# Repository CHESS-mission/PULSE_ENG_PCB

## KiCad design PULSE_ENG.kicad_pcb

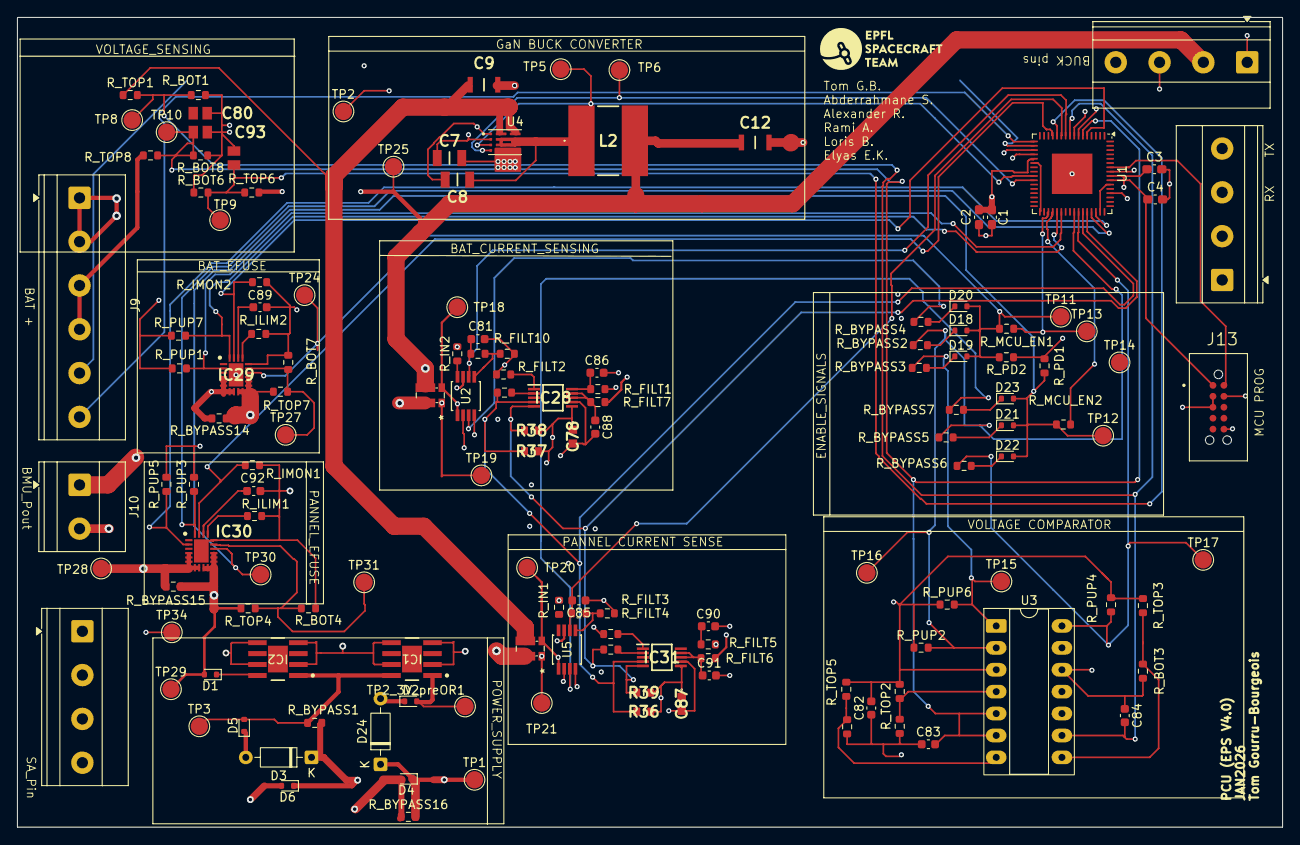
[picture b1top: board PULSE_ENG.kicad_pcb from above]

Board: 4 copper layers, 146.7 x 93.9 mm, 144 parts (0 on the bottom side), 84 nets.

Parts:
C1, C4: 100nF; C_0603_1608Metric_Pad1.08x0.95mm_HandSolder
C2, C3: 10uF; C_0603_1608Metric_Pad1.08x0.95mm_HandSolder
C7, C8: CAPC3216X170N
C9: 4.7uF; CAPC3216X180N
C12: C3216X8L1E106K160AE; CAPC3216X180N
C78, C87: 0.1μF; C0603
C79, C80, C93: 10nF; CAPC2012X145N
C81, C82, C83, C84, C85, C86, C88, C89, C90, C91, C92: 100nF; C_0603_1608Metric
D1, D2, D4, D5, D6, D18, D19, D20, D21, D22, D23: 1N4148WT; D_SOD-523
D3, D24: 1N5711; D_DO-35_SOD27_P7.62mm_Horizontal
IC1: TPS7B8733QDDARQ1; DDA0008J-IPC_B
IC2: TPS7B8750QDDARQ1; DDA0008J-IPC_B
IC28, IC31: INA226AIDGSR; SOP50P490X110-10N
IC29, IC30: TPS25940ARVCR; QFN50P300X400X80-21N
J8, J11, J12: Screw_Terminal_01x04; TerminalBlock_Phoenix_MKDS-1,5-4-5.08_1x04_P5.08mm_Horizont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
J9: Screw_Terminal_01x06; TerminalBlock_Phoenix_MKDS-1,5-6-5.08_1x06_P5.08mm_Horizont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
J10: Screw_Terminal_01x01; TerminalBlock_Phoenix_MKDS-1,5-2-5.08_1x02_P5.08mm_Horizont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
J13: TC2050-IDC-NL; TAG-CONNECT_TC2050-IDC-NL
L2: 78404084470
R36, R37, R38, R39: 10KΩ; RESC1608X55N
R_ADD_CONFIG1, R_ADD_CONFIG2, R_ADD_CONFIG3, R_ADD_CONFIG4: 0; R_0603_1608Metric
R_BAT_SHUNT1: 20mOhm; R_Shunt_Vishay_WSKW0612
R_BOT1, R_BOT2, R_BOT3, R_BOT5, R_BOT6, R_BOT8: 180k; R_0603_1608Metric
R_BOT4, R_BOT7: 100k; R_0603_1608Metric
R_BYPASS1, R_BYPASS2, R_BYPASS3, R_BYPASS4, R_BYPASS5, R_BYPASS6, R_BYPASS7, R_BYPASS14, R_BYPASS15, R_BYPASS16: 0; R_0603_1608Metric
R_FILT1, R_FILT5, R_FILT6, R_FILT7: 10; R_0603_1608Metric
R_FILT2, R_FILT4: 2.61k; R_0603_1608Metric
R_FILT3, R_FILT10: 402; R_0603_1608Metric
R_ILIM1: 24k; R_0603_1608Metric
R_ILIM2: 16.9k; R_0603_1608Metric
R_IMON1, R_IMON2: 4k; R_0603_1608Metric
R_IN1, R_IN2: 100; R_0603_1608Metric
R_MCU_EN1, R_MCU_EN2: 1k; R_0603_1608Metric
R_PANNEL_SHUNT1: 20mOhm; R_Shunt_Vishay_WSKW0612
R_PD1, R_PD2: 100k; R_0603_1608Metric
R_PUP1, R_PUP2, R_PUP3, R_PUP4, R_PUP5, R_PUP6, R_PUP7: 10k; R_0603_1608Metric
R_TOP1, R_TOP6, R_TOP8: 680k; R_0603_1608Metric
R_TOP2: 147k; R_0603_1608Metric
R_TOP3: 68k; R_0603_1608Metric
R_TOP4, R_TOP7: 681; R_0603_1608Metric
R_TOP5: 247k; R_0603_1608Metric
TP1: 3V3_rail; TestPoint_Pad_D2.0mm
TP2: 12Vin_buck; TestPoint_Pad_D2.0mm
TP2_3V_preOR1: TestPoint_Pad_D2.0mm
TP3: 5V_preOR; TestPoint_Pad_D2.0mm
TP5: PWM_H; TestPoint_Pad_D2.0mm
TP6: PWM_L; TestPoint_Pad_D2.0mm
TP8: VPANNEL_SENSE; TestPoint_Pad_D2.0mm
TP9: VCHG_RAIL_SENSE; TestPoint_Pad_D2.0mm
TP10: VBAT_SENSE; TestPoint_Pad_D2.0mm
TP11: BAT_EFUSE_EN; TestPoint_Pad_D2.0mm
TP12: PANNEL_EFUSE_EN; TestPoint_Pad_D2.0mm
TP13: MCU_BAT_EFUSE_EN; TestPoint_Pad_D2.0mm
TP14: MCU_PANNEL_EFUSE_EN; TestPoint_Pad_D2.0mm
TP15: BAT_UVP; TestPoint_Pad_D2.0mm
TP16: BAT_OVP; TestPoint_Pad_D2.0mm
TP17: PANNEL_OVP; TestPoint_Pad_D2.0mm
TP18: BAT_SHUNT_OUT; TestPoint_Pad_D2.0mm
TP19: BAT_SHUNT_IN; TestPoint_Pad_D2.0mm
TP20: PANNEL_SHUNT_OUT; TestPoint_Pad_D2.0mm
TP21: PANNEL_SHUNT_IN; TestPoint_Pad_D2.0mm
TP24: eFUSE_EN; TestPoint_Pad_D2.0mm
TP25: Buck_out; TestPoint_Pad_D2.0mm
TP27: eFUSE_OVP; TestPoint_Pad_D2.0mm
TP28: P_Vout_Protected; TestPoint_Pad_D2.0mm
TP29: PVin; TestPoint_Pad_D2.0mm
TP30: eFuse_EN; TestPoint_Pad_D2.0mm
TP31: eFuse_OVP; TestPoint_Pad_D2.0mm
TP34: GND; TestPoint_Pad_D2.0mm
U1: ATSAMD21J17D-M; QFN-64-1EP_9x9mm_P0.5mm_EP4.7x4.7mm
U2, U5: LT6108IMS8-1-TRPBF; MSOP-8_MS_LIT
U3: LM139ADRG4; CERDIP-14_W7.62mm_SideBrazed_LongPads_Socket
U4: EPC2152; VREG_EPC2152ENGRT

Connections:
12V_1: C7.1, J11.1, TP2.1, U4.2 (Vdd12)
/3.3V: C78.1, IC28.6 (VS), R37.2, R38.2, R_PUP1.2, R_PUP7.2
/5V: D3.1 (K), D6.1 (K), R_BYPASS1.2
/BAT_EFUSE_EN: D18.2 (A), D19.2 (A), D20.2 (A), IC29.14 (EN), R_MCU_EN1.1, R_PD2.2, TP11.1, TP24.1
/BAT_EFUSE_FLT: IC29.20 (~FLT), R_PUP7.1, U1.37 (PA18)
/BAT_EFUSE_IMON: IC29.19 (IMON), R_IMON2.2, U1.5 (PB04)
/BAT_EFUSE_PGOOD: IC29.2 (PGOOD), R_PUP1.1, U1.38 (PA19)
/BAT_OVP_FLAG: R_BYPASS2.1, R_BYPASS5.1, R_PUP2.2, TP16.1, U1.41 (PA20), U3.2 (2OUT)
/BAT_SHUNT_IN: R_BAT_SHUNT1.3, R_FILT1.1, R_IN2.2, TP19.1, U2.7 (V+)
/BAT_SHUNT_OUT: R_BAT_SHUNT1.2, R_FILT7.1, TP18.1, U2.1 (SENSELO)
/BAT_UVP_FLAG: R_BYPASS3.1, R_PUP6.2, TP15.1, U3.1 (1OUT)
/Battery_protection_and_sensing/P_Vout_Protected: IC29.4 (OUT_1), IC29.5 (OUT_2), IC29.6 (OUT_3), IC29.7 (OUT_4), IC29.8 (OUT_5), J10.1, R_BYPASS14.2
/EPS_Power_Supply/3V3_LDO: D2.2 (A), IC1.1 (OUT), TP2_3V_preOR1.1
/EPS_Power_Supply/5V_LDO: D5.2 (A), IC1.8 (IN), IC2.1 (OUT), R_BYPASS1.1, TP3.1
/GAN_PWM_H: TP5.1, U1.25 (PB12), U4.3 (HSin)
/GAN_PWM_L: TP6.1, U1.26 (PB13), U4.4 (LSin)
/HEATER_SWITCH: J9.6, U1.17 (PA08)
/I_BAT_ANA: C81.2, R_FILT10.2, U1.10 (PB07), U2.6 (OUTA)
/I_PANNEL_ANA: C85.2, R_FILT3.2, U1.11 (PB08), U5.6 (OUTA)
/MCU_BAT_EFUSE_EN: R_MCU_EN1.2, TP13.1, U1.35 (PA16)
/MCU_PANNEL_EFUSE_EN: R_MCU_EN2.2, TP14.1, U1.36 (PA17)
/PANNEL_EFUSE_EN: D21.2 (A), D22.2 (A), D23.2 (A), IC30.14 (EN), R_MCU_EN2.1, R_PD1.2, TP12.1, TP30.1
/PANNEL_OVP_FLAG: R_BYPASS6.1, R_PUP4.1, TP17.1, U1.42 (PA21), U3.14 (OUT3)
/PANNEL_SHUNT_IN: R_FILT6.1, R_IN1.2, R_PANNEL_SHUNT1.3, TP21.1, U5.7 (V+)
/PANNEL_SHUNT_OUT: R_FILT5.1, R_PANNEL_SHUNT1.2, TP20.1, U5.1 (SENSELO)
/PAN_EFUSE_FLT: IC30.20 (~FLT), R_PUP3.1, U1.45 (PA24)
/PAN_EFUSE_IMON: IC30.19 (IMON), R_IMON1.2, U1.13 (PA04)
/PAN_EFUSE_PGOOD: IC30.2 (PGOOD), R_PUP5.1, U1.46 (PA25)
/PCU_Control/BAT_OVC: R_BYPASS4.1, U2.3 (OUTC)
/PCU_Control/PANNEL_OVC: R_BYPASS7.1, U5.3 (OUTC)
/POWER_SWITCH: J9.5, U1.18 (PA09)
/Pannel_protection_and_sensing/PV_protected: IC30.4 (OUT_1), IC30.5 (OUT_2), IC30.6 (OUT_3), IC30.7 (OUT_4), IC30.8 (OUT_5), R_BYPASS15.2, R_PANNEL_SHUNT1.4, TP28.1
/RESET: J13.6, U1.52 (~RESET)
/TEST_3V_PDU: D4.2 (A), J8.2, R_BYPASS16.1
/TEST_5V_PDU: D6.2 (A), J8.3
/TEST_Pin_SA: D1.2 (A), IC30.9 (IN_1), IC30.10 (IN_2), IC30.11 (IN_3), IC30.12 (IN_4), IC30.13 (IN_5), J8.4, R_BYPASS15.1, R_TOP4.1, TP29.1
/UART1_RX: J12.3, U1.20 (PA11)
/UART1_TX: J12.4, U1.19 (PA10)
/VBAT_SENSE: C83.2, C93.1, R_BOT8.2, R_TOP8.2, TP10.1, U1.6 (PB05), U3.5 (2IN+), U3.6 (1IN-)
/VCHG_RAIL_SENSE: C79.1, R_BOT6.2, R_TOP6.2, TP9.1, U1.12 (PB09)
/VPANNEL_SENSE: C80.1, C84.2, R_BOT1.2, R_TOP1.2, TP8.1, U1.9 (PB06), U3.9 (3IN+)
/V_pannel_protected: C9.2, R_PANNEL_SHUNT1.1, R_TOP1.1, U4.5 (Vin), U4.9 (Vin)
/Vbat: J9.3, J9.4, R_BAT_SHUNT1.4, R_TOP8.1
/Vout_BUCK: C12.2, IC29.9 (IN_1), IC29.10 (IN_2), IC29.11 (IN_3), IC29.12 (IN_4), IC29.13 (IN_5), J11.2, L2.2, R_BAT_SHUNT1.1, R_BYPASS14.1, R_TOP6.1, R_TOP7.1, TP25.1
GND: C1.2, C2.2, C3.2, C4.2, C7.2, C78.2, C79.2, C80.2, C81.1, C82.2, C83.1, C84.1, C85.1, C86.2, C87.2, C88.2, C89.1, C90.2, C91.2, C92.1, C93.2, IC1.2 (NC_1), IC1.4 (NC_2), IC1.5 (GND), IC1.7 (NC_3), IC2.2 (NC_1), IC2.4 (NC_2), IC2.5 (GND), IC2.7 (NC_3), IC28.7 (GND), IC29.16 (GND), IC29.21 (EPAD), IC30.16 (GND), IC30.21 (EPAD), IC31.7 (GND), J8.1, J9.1, J9.2, J11.4, J12.1, J12.2, J13.2, J13.3, R_ADD_CONFIG2.1, R_ADD_CONFIG4.1, R_BOT1.1, R_BOT2.1, R_BOT3.1, R_BOT4.2, R_BOT5.1, R_BOT6.1, R_BOT7.2, R_BOT8.1, R_FILT2.1, R_FILT4.1, R_ILIM1.2, R_ILIM2.2, R_IMON1.1, R_IMON2.1, R_PD1.1, R_PD2.1, TP34.1, U1.7 (GNDANA), U1.65 (EP), U2.4 (V-), U3.12 (GND), U4.8 (Vss), U5.4 (V-)
unnamed: C8.1, L2.1, U4.6 (SW), U4.7 (SW), U4.10 (SW), U4.11 (SW)
unnamed: C9.1, C12.1, U4.12 (Vss)
unnamed: D1.1 (K), IC2.8 (IN)
unnamed: D2.1 (K), D24.2 (A)
unnamed: D3.2 (A), D5.1 (K)
unnamed: D18.1 (K), R_BYPASS2.2
unnamed: D19.1 (K), R_BYPASS3.2
unnamed: D20.1 (K), R_BYPASS4.2
unnamed: D21.1 (K), R_BYPASS5.2
unnamed: D22.1 (K), R_BYPASS6.2
unnamed: D23.1 (K), R_BYPASS7.2
unnamed: IC28.2 (A0), R_ADD_CONFIG1.2
unnamed: IC28.1 (A1), R_ADD_CONFIG4.2
unnamed: C86.1, IC28.10 (IN+), R_FILT7.2
unnamed: C88.1, IC28.8 (VBUS), IC28.9 (IN-), R_FILT1.2
unnamed: C89.2, IC29.18 (DVDT)
unnamed: IC29.17 (ILIM), R_ILIM2.1
unnamed: IC29.15 (OVP), R_BOT7.1, R_TOP7.2, TP27.1
unnamed: C92.2, IC30.18 (DVDT)
unnamed: IC30.17 (ILIM), R_ILIM1.1
unnamed: IC30.15 (OVP), R_BOT4.1, R_TOP4.2, TP31.1
unnamed: IC31.2 (A0), R_ADD_CONFIG3.2
unnamed: IC31.1 (A1), R_ADD_CONFIG2.2
unnamed: C90.1, IC31.10 (IN+), R_FILT5.2
unnamed: C91.1, IC31.8 (VBUS), IC31.9 (IN-), R_FILT6.2
unnamed: C8.2, J11.3, U4.1 (Vdd12F)
unnamed: U1.22 (GND), U1.33 (GND), U1.47 (GND), U1.54 (GND)
unnamed: R_FILT2.2, R_FILT10.1, U2.5 (INC)
unnamed: R_IN2.1, U2.8 (SENSEHI)
unnamed: R_BOT5.2, R_TOP5.1, U3.7 (1IN+)
unnamed: R_BOT2.2, R_TOP2.1, U3.4 (2IN-)
unnamed: R_BOT3.2, R_TOP3.1, U3.8 (3IN-)
unnamed: R_FILT3.1, R_FILT4.2, U5.5 (INC)
unnamed: R_IN1.1, U5.8 (SENSEHI)
SCL2: IC28.5 (SCL), IC31.5 (SCL), R38.1, R39.1, R_ADD_CONFIG3.1, U1.44 (PA23)
SDA2: IC28.4 (SDA), IC31.4 (SDA), R36.1, R37.1, R_ADD_CONFIG1.1, U1.43 (PA22)
SWCLK: J13.9, U1.57 (PA30)
SWDIO: J13.10, U1.58 (PA31)
VDDANA: C1.1, C2.1, C3.1, C4.1, C82.1, C87.1, D4.1 (K), D24.1 (K), IC31.6 (VS), J13.1, R36.2, R39.2, R_BYPASS16.2, R_PUP2.1, R_PUP3.2, R_PUP4.2, R_PUP5.2, R_PUP6.1, R_TOP2.2, R_TOP3.2, R_TOP5.2, TP1.1, U1.8 (VDDANA), U1.21 (VDDIO), U1.56 (VDDIN), U2.2 (EN/*RST), U3.3 (VCC), U5.2 (EN/*RST)

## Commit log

2025-11-24 add pdu libery
2025-11-24 Create .gitignore for KiCAD project files
    Added ignore patterns for KiCAD project files and temporary files.
2025-11-25 addaped pdu 3d filse fodler paht
2025-11-25 adapted footprint pahts
2025-11-26 added epc2152
2025-11-27 added schematics hirarchie
2025-11-27 deleted backup
2025-11-27 changed epc gan symbol
2025-12-01 Power supply
2025-12-01 .lck in gitignore
2025-12-01 PDU_SCHEMATICS_v01
2025-12-01 Add PCU buck converter section and notebook link
2025-12-01 buck
2025-12-01 Update .gitignore to include auto_saved_files
    Add entries to ignore auto-saved files in KiCAD projects.
2025-12-01 PDU_SCHEMATICS_v02 changes in the 3D
2025-12-01 UART ic added, SWD pins mapped
2025-12-03 Battery pack P1 connector
    Still needs to be mapped to mcu, MAY NEED MIRRORING (couldn't understand indexing order logic :( )
2025-12-03 Created a page for BAT eFuse and current sensing. Updated the cControl page with part of the harware cutoff
2025-12-03 Created a page for PANNEL efuse, modifiel all to local labels, functionally finished
2025-12-04 modifications on PDU
2025-12-04 added 3d bat con
2025-12-04 Some edits
2025-12-04 Modification of ROOT sheet blocks
2025-12-04 Final schematics pdu
2025-12-04 wrong folder
2025-12-05 rearangment
2025-12-07 pcb trial
2025-12-07 test layout
2025-12-08 Adjusting footprints of components
2025-12-11 Big final PCU PCB design
2025-12-11 Final addings
2025-12-13 small power supply modification
2025-12-13 Replaced Oring simple diodes with schottky
2025-12-15 changed 90deg traces, added est logo
2025-12-16 Modofications asked and BOM
2025-12-17 changed mcu power suppl
2026-02-19 Tom version
2026-02-22 lastest
2026-02-26 fixed LDO
